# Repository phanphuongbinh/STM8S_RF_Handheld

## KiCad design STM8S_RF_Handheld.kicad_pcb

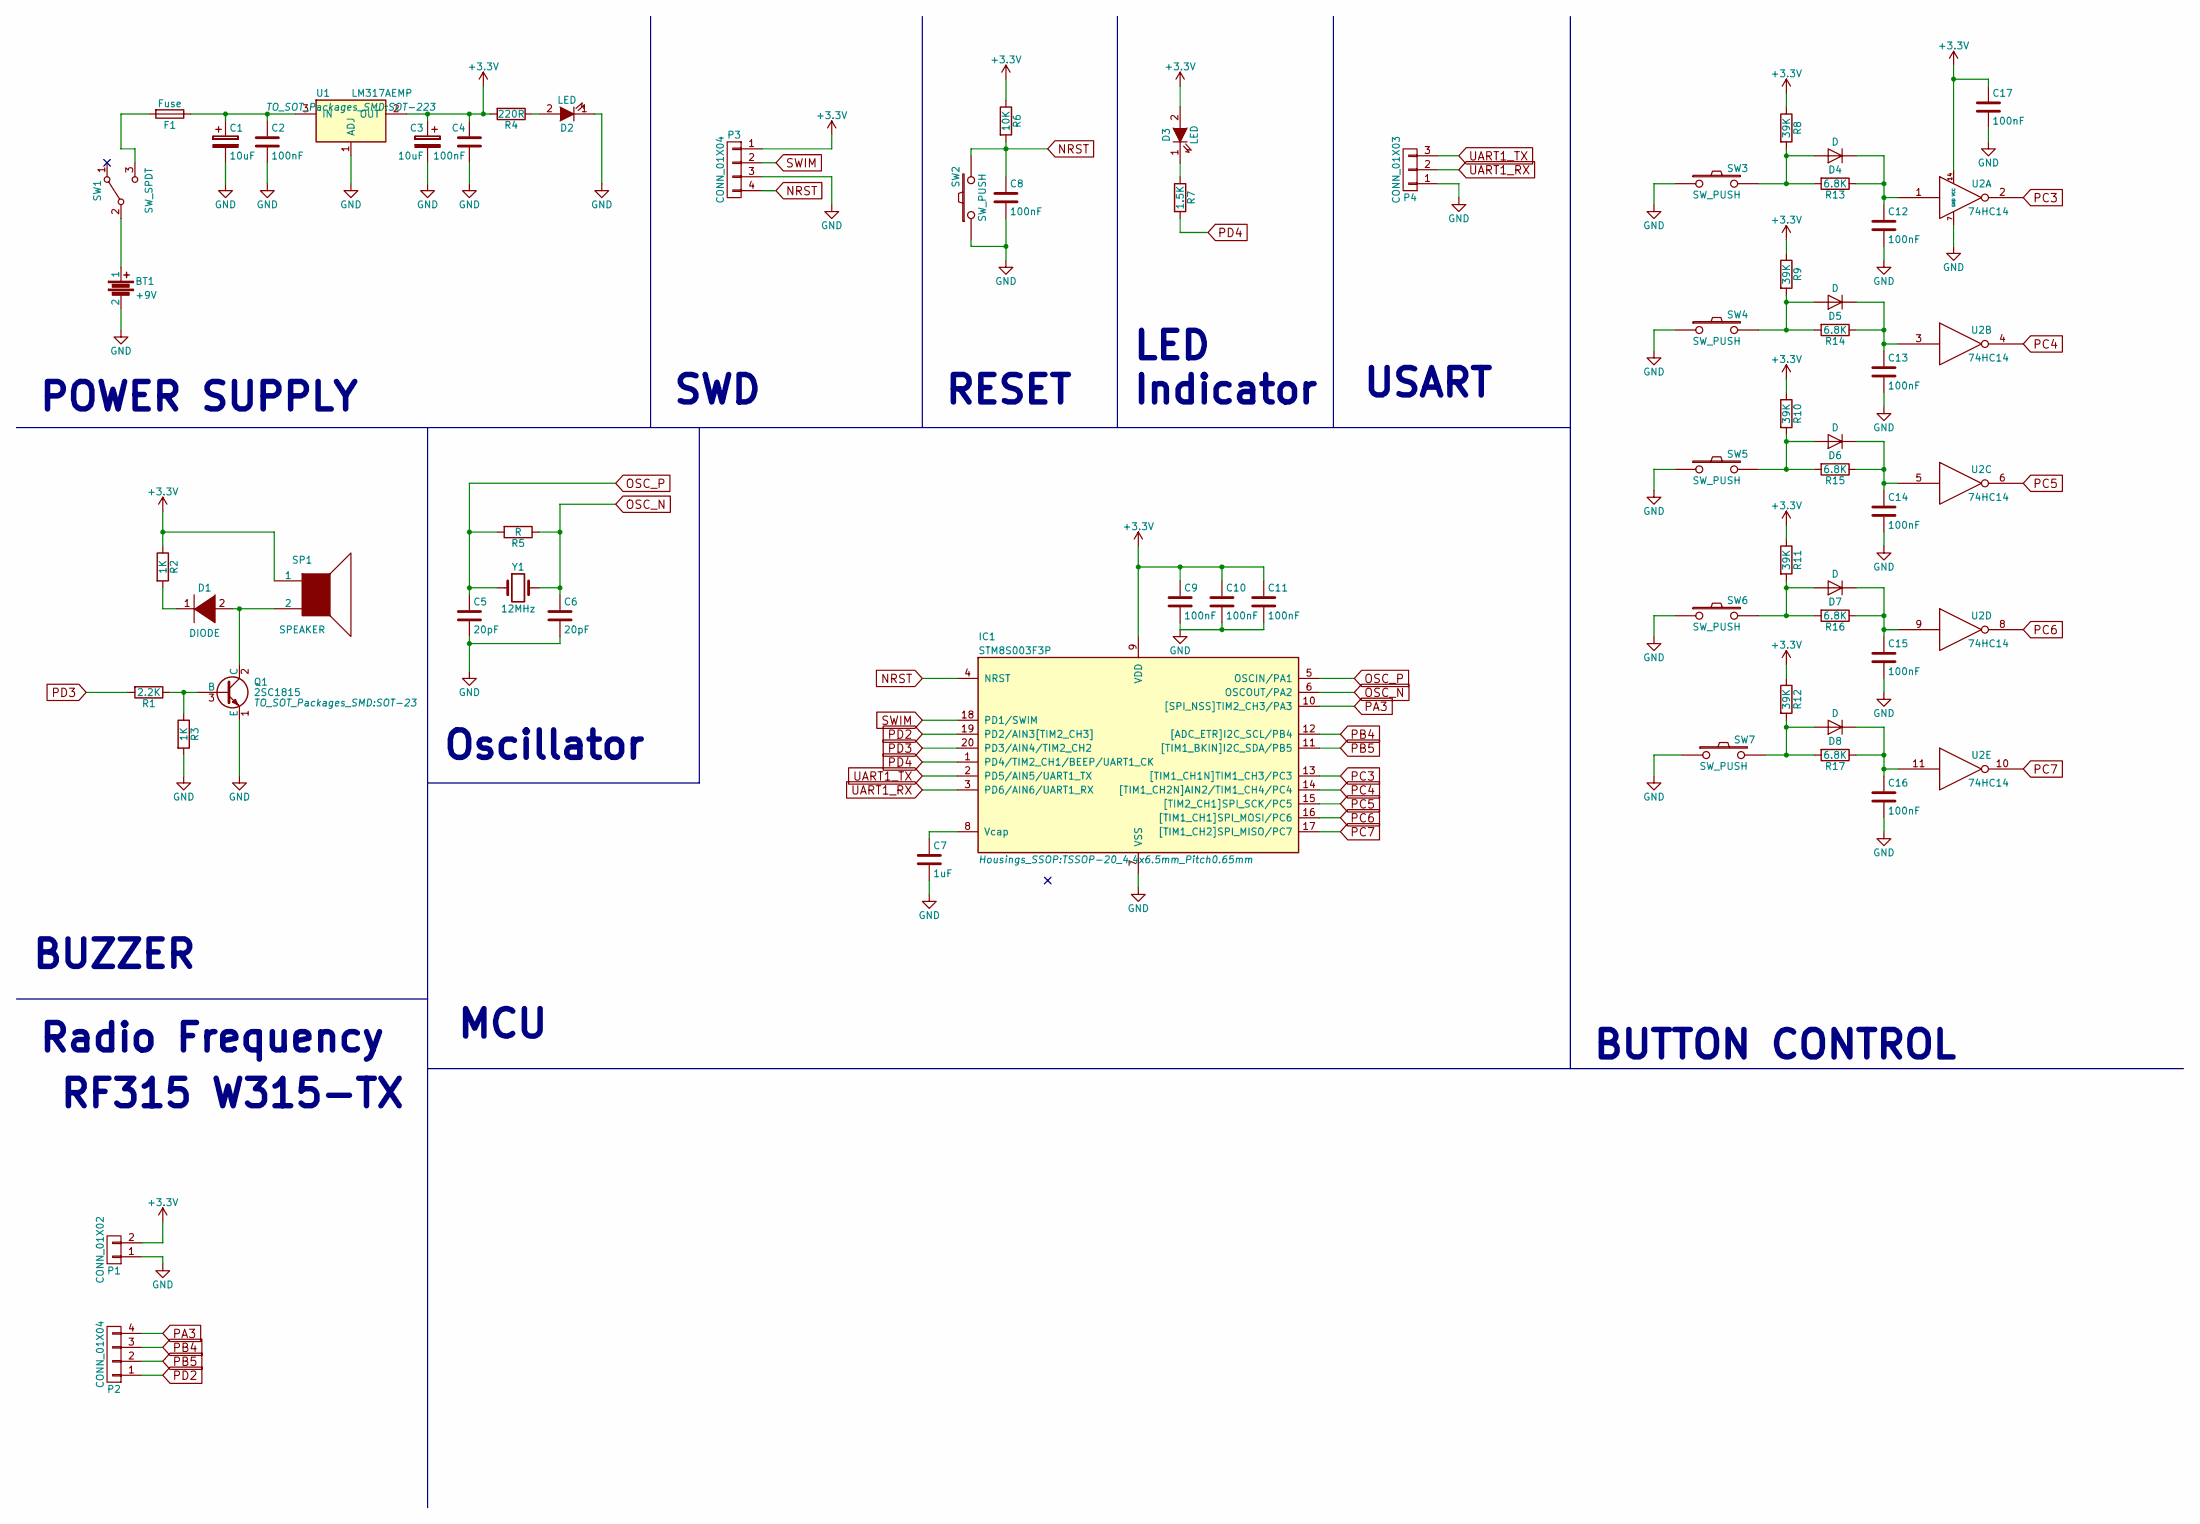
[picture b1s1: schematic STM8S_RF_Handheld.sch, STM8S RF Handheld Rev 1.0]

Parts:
BT1: +9V; AK300-2
C1, C3: 10uF; c_elec_4x5.8
C2, C4, C8, C9, C10, C11, C12, C13, C14, C15, C16, C17: 100nF; C_0603_HandSoldering
C5, C6: 20pF; C_0603_HandSoldering
C7: 1uF; C_0603_HandSoldering
D1: DIODE; SMA_Handsoldering
D2, D3: LED; LED_0603
D4, D5, D6, D7, D8: D; SMA_Handsoldering
F1: Fuse; Fuseholder5x20_horiz_open_lateral_Type-II
IC1: STM8S003F3P; TSSOP-20_4.4x6.5mm_Pitch0.65mm
P1: CONN_01X02; Pin_Header_Straight_1x02
P2, P3: CONN_01X04; Pin_Header_Straight_1x04
P4: CONN_01X03; Pin_Header_Straight_1x03
Q1: 2SC1815; SOT-23
R1: 2.2K; R_0603_HandSoldering
R2, R3: 1K; R_0603_HandSoldering
R4: 220R; R_0603_HandSoldering
R5: R; R_0603_HandSoldering
R6: 10K; R_0603_HandSoldering
R7: 1.5K; R_0603_HandSoldering
R8, R9, R10, R11, R12: 39K; R_0603_HandSoldering
R13, R14, R15, R16, R17: 6.8K; R_0603_HandSoldering
SP1: SPEAKER; Buzzer_12x9.5RM7.6
SW1: SW_SPDT
SW2: SW_PUSH; SW_SPST_FSMSM
SW3, SW4, SW5, SW6, SW7: SW_PUSH; SW_PUSH-12mm
U1: LM317AEMP; SOT-223
U2: 74HC14; SOIC-14_3.9x8.7mm_Pitch1.27mm
Y1: 12MHz; Crystal_HC49-SD_SMD

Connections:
+3V3: C3.1, C4.1, C9.1, C10.1, C11.1, C17.1, D3.2 (A), IC1.9 (VDD), P1.2, P3.1, R2.1, R4.2, R6.1, R8.1, R9.1, R10.1, R11.1, R12.1, SP1.1, U1.2 (OUT), U2.14 (VCC)
GND: BT1.2, C1.2, C2.2, C3.2, C4.2, C5.2, C6.2, C7.2, C8.2, C9.2, C10.2, C11.2, C12.2, C13.2, C14.2, C15.2, C16.2, C17.2, D2.1 (K), IC1.7 (VSS), P1.1, P3.3, P4.1, Q1.1 (E), R3.2, SW2.1, SW3.1, SW4.1, SW5.1, SW6.1, SW7.1, U1.1 (ADJ), U2.7 (GND)
NRST: C8.1, IC1.4 (NRST), P3.4, R6.2, SW2.2
unnamed: BT1.1, SW1.2 (B)
unnamed: C1.1, C2.1, F1.1, U1.3 (IN)
unnamed: C7.1, IC1.8 (Vcap)
unnamed: C12.1, D4.1 (K), R13.1, U2.1
unnamed: C13.1, D5.1 (K), R14.1, U2.3
unnamed: C14.1, D6.1 (K), R15.1, U2.5
unnamed: C15.1, D7.1 (K), R16.1, U2.9
unnamed: C16.1, D8.1 (K), R17.1, U2.11
unnamed: D1.1 (K), R2.2
unnamed: D1.2 (A), Q1.2 (C), SP1.2
unnamed: D2.2 (A), R4.1
unnamed: D3.1 (K), R7.1
unnamed: D4.2 (A), R8.2, R13.2, SW3.2
unnamed: D5.2 (A), R9.2, R14.2, SW4.2
unnamed: D6.2 (A), R10.2, R15.2, SW5.2
unnamed: D7.2 (A), R11.2, R16.2, SW6.2
unnamed: D8.2 (A), R12.2, R17.2, SW7.2
unnamed: F1.2, SW1.3 (C)
unnamed: Q1.3 (B), R1.1, R3.1
OSC_N: C6.1, IC1.6 (OSCOUT/PA2), R5.1, Y1.2
OSC_P: C5.1, IC1.5 (OSCIN/PA1), R5.2, Y1.1
PA3: IC1.10 ([SPI_NSS]TIM2_CH3/PA3), P2.4
PB4: IC1.12 ([ADC_ETR]I2C_SCL/PB4), P2.3
PB5: IC1.11 ([TIM1_BKIN]I2C_SDA/PB5), P2.2
PC3: IC1.13 ([TIM1_CH1N]TIM1_CH3/PC3), U2.2
PC4: IC1.14 ([TIM1_CH2N]AIN2/TIM1_CH4/PC4), U2.4
PC5: IC1.15 ([TIM2_CH1]SPI_SCK/PC5), U2.6
PC6: IC1.16 ([TIM1_CH1]SPI_MOSI/PC6), U2.8
PC7: IC1.17 ([TIM1_CH2]SPI_MISO/PC7), U2.10
PD2: IC1.19 (PD2/AIN3[TIM2_CH3]), P2.1
PD3: IC1.20 (PD3/AIN4/TIM2_CH2), R1.2
PD4: IC1.1 (PD4/TIM2_CH1/BEEP/UART1_CK), R7.2
SWIM: IC1.18 (PD1/SWIM), P3.2
UART1_RX: IC1.3 (PD6/AIN6/UART1_RX), P4.2
UART1_TX: IC1.2 (PD5/AIN5/UART1_TX), P4.3

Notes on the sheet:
BUZZER
BUTTON CONTROL
MCU
USART
SWD
RESET
POWER SUPPLY
Oscillator
LED Indicator
Radio Frequency
RF315 W315-TX

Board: 2 copper layers, 61 parts (27 on the bottom side), 38 nets, no tracks yet.

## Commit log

2016-11-28 First commit.
2016-12-05 Change PCB size.
2016-12-05 Add new Pcbdxf file for PCB size.
